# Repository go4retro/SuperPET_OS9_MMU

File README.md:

# SuperPET_OS9_MMU
TPUG OS9 MMU Reproduction

 - [Information and Software](http://mikenaberezny.com/hardware/superpet/super-os9-mmu/)
 - [Purchase a Kit](http://store.go4retro.com/superpet-os-9-mmu/)

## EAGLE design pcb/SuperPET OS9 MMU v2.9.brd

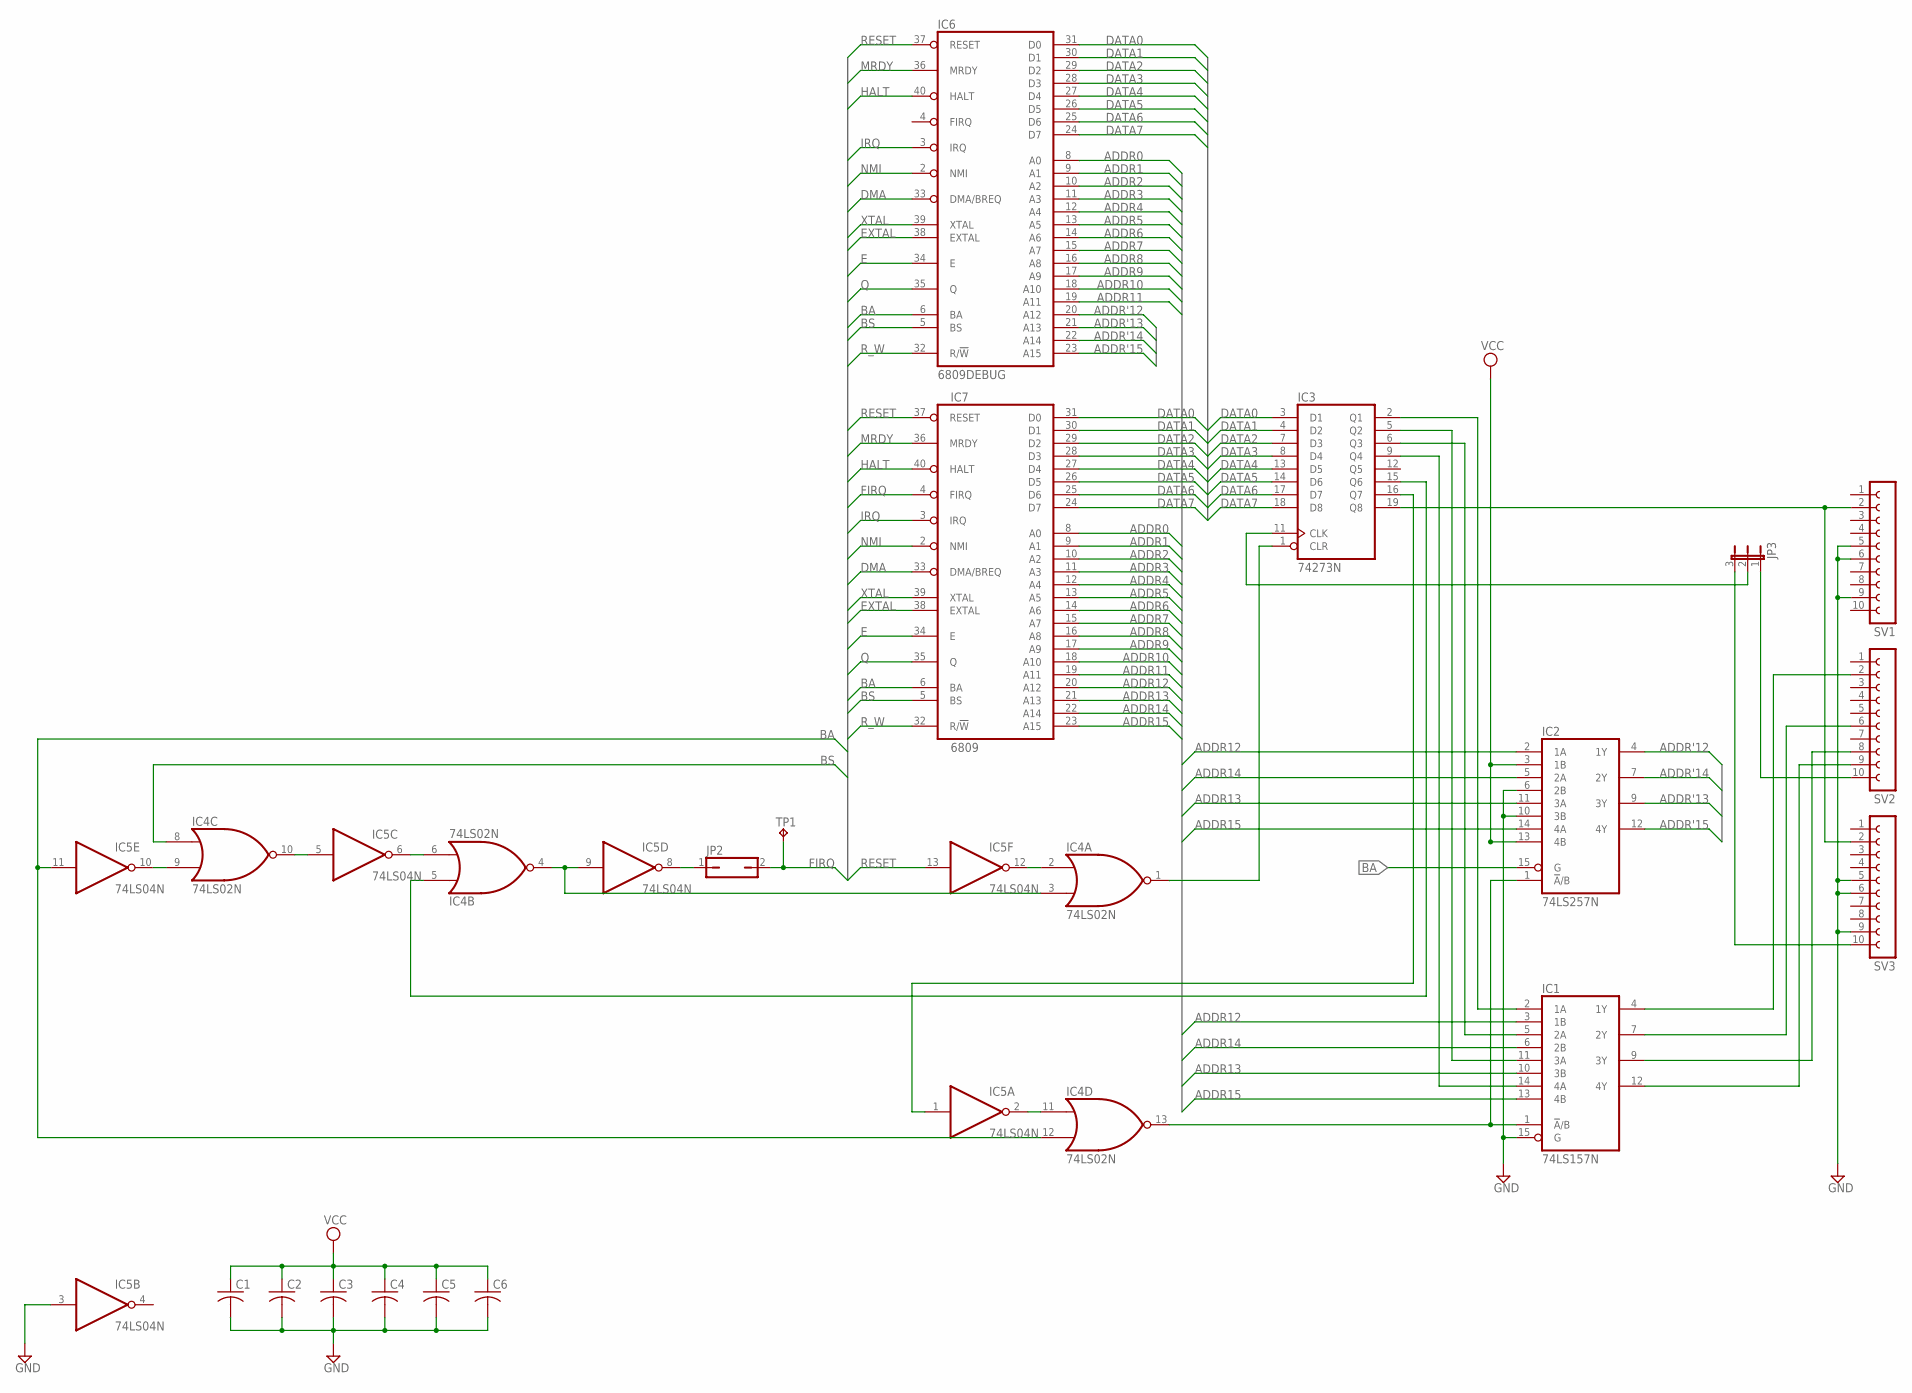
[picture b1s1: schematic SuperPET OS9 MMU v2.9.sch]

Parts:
C1, C2, C3, C4, C5, C6: C-US025-025X050; C025-025X050
IC1: 74LS157N; DIL16
IC2: 74LS257N; DIL16
IC3: 74273N; DIL20
IC4: 74LS02N; DIL14
IC5: 74LS04N; DIL14
IC6: 6809DEBUG; DIL40
IC7: 6809; DIL40
JP2: JP1Q; JP1
JP3: JP2E; JP2
SV1, SV2, SV3: FE10-1; FE10
TP1: TPPAD1-17; P1-17

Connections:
ADDR0: IC6.8 (A0), IC7.8 (A0)
ADDR1: IC6.9 (A1), IC7.9 (A1)
ADDR2: IC6.10 (A2), IC7.10 (A2)
ADDR3: IC6.11 (A3), IC7.11 (A3)
ADDR4: IC6.12 (A4), IC7.12 (A4)
ADDR5: IC6.13 (A5), IC7.13 (A5)
ADDR6: IC6.14 (A6), IC7.14 (A6)
ADDR7: IC6.15 (A7), IC7.15 (A7)
ADDR8: IC6.16 (A8), IC7.16 (A8)
ADDR9: IC6.17 (A9), IC7.17 (A9)
ADDR10: IC6.18 (A10), IC7.18 (A10)
ADDR11: IC6.19 (A11), IC7.19 (A11)
ADDR12: IC1.3 (1B), IC2.2 (1A), IC7.20 (A12)
ADDR13: IC1.10 (3B), IC2.11 (3A), IC7.21 (A13)
ADDR14: IC1.6 (2B), IC2.5 (2A), IC7.22 (A14)
ADDR15: IC1.13 (4B), IC2.14 (4A), IC7.23 (A15)
ADDR'12: IC2.4 (1Y), IC6.20 (A12)
ADDR'13: IC2.9 (3Y), IC6.21 (A13)
ADDR'14: IC2.7 (2Y), IC6.22 (A14)
ADDR'15: IC2.12 (4Y), IC6.23 (A15)
BA: IC2.15 (G), IC4.12 (I1), IC5.11 (I), IC6.6 (BA), IC7.6 (BA)
BS: IC4.8 (I0), IC6.5 (BS), IC7.5 (BS)
DATA0: IC3.3 (D1), IC6.31 (D0), IC7.31 (D0)
DATA1: IC3.4 (D2), IC6.30 (D1), IC7.30 (D1)
DATA2: IC3.7 (D3), IC6.29 (D2), IC7.29 (D2)
DATA3: IC3.8 (D4), IC6.28 (D3), IC7.28 (D3)
DATA4: IC3.13 (D5), IC6.27 (D4), IC7.27 (D4)
DATA5: IC3.14 (D6), IC6.26 (D5), IC7.26 (D5)
DATA6: IC3.17 (D7), IC6.25 (D6), IC7.25 (D6)
DATA7: IC3.18 (D8), IC6.24 (D7), IC7.24 (D7)
DMA: IC6.33 (DMA/BREQ), IC7.33 (DMA/BREQ)
E: IC6.34 (E), IC7.34 (E)
EXTAL: IC6.38 (EXTAL), IC7.38 (EXTAL)
FIRQ: IC7.4 (FIRQ), JP2.2, TP1.1
GND: C1.2, C2.2, C3.2, C4.2, C5.2, C6.2, IC1.8 (GND), IC1.15 (G), IC2.6 (2B), IC2.8 (GND), IC2.10 (3B), IC3.10 (GND), IC4.7 (GND), IC5.3 (I), IC5.7 (GND), IC6.1 (GND), IC7.1 (GND), SV1.5, SV1.6, SV1.9, SV3.5, SV3.6, SV3.9
HALT: IC6.40 (HALT), IC7.40 (HALT)
IRQ: IC6.3 (IRQ), IC7.3 (IRQ)
MRDY: IC6.36 (MRDY), IC7.36 (MRDY)
unnamed: IC1.1 (!A!/B), IC2.1 (!A!/B), IC4.13 (O)
unnamed: IC3.1 (CLR), IC4.1 (O)
unnamed: IC4.2 (I0), IC5.12 (O)
unnamed: IC5.8 (O), JP2.1
unnamed: IC4.3 (I1), IC4.4 (O), IC5.9 (I)
unnamed: IC3.15 (Q6), IC4.5 (I0)
unnamed: IC4.6 (I1), IC5.6 (O)
unnamed: IC4.10 (O), IC5.5 (I)
unnamed: IC4.9 (I1), IC5.10 (O)
unnamed: IC4.11 (I0), IC5.2 (O)
unnamed: IC3.16 (Q7), IC5.1 (I)
unnamed: IC1.2 (1A), IC3.2 (Q1)
unnamed: IC1.14 (4A), IC3.9 (Q4)
unnamed: IC1.11 (3A), IC3.5 (Q2)
unnamed: IC1.7 (2Y), SV2.6
unnamed: IC3.19 (Q8), SV1.2, SV3.2
unnamed: IC1.12 (4Y), SV2.9
unnamed: JP3.1, SV2.10
unnamed: IC3.11 (CLK), JP3.2
unnamed: JP3.3, SV3.10
unnamed: IC1.5 (2A), IC3.6 (Q3)
unnamed: IC1.4 (1Y), SV2.2
unnamed: IC1.9 (3Y), SV2.8
NMI: IC6.2 (NMI), IC7.2 (NMI)
Q: IC6.35 (Q), IC7.35 (Q)
RESET: IC5.13 (I), IC6.37 (RESET), IC7.37 (RESET)
R_W: IC6.32 (R/!W), IC7.32 (R/!W)
VCC: C1.1, C2.1, C3.1, C4.1, C5.1, C6.1, IC1.16 (VCC), IC2.3 (1B), IC2.13 (4B), IC2.16 (VCC), IC3.20 (VCC), IC4.14 (VCC), IC5.14 (VCC), IC6.7 (VCC), IC7.7 (VCC)
XTAL: IC6.39 (XTAL), IC7.39 (XTAL)

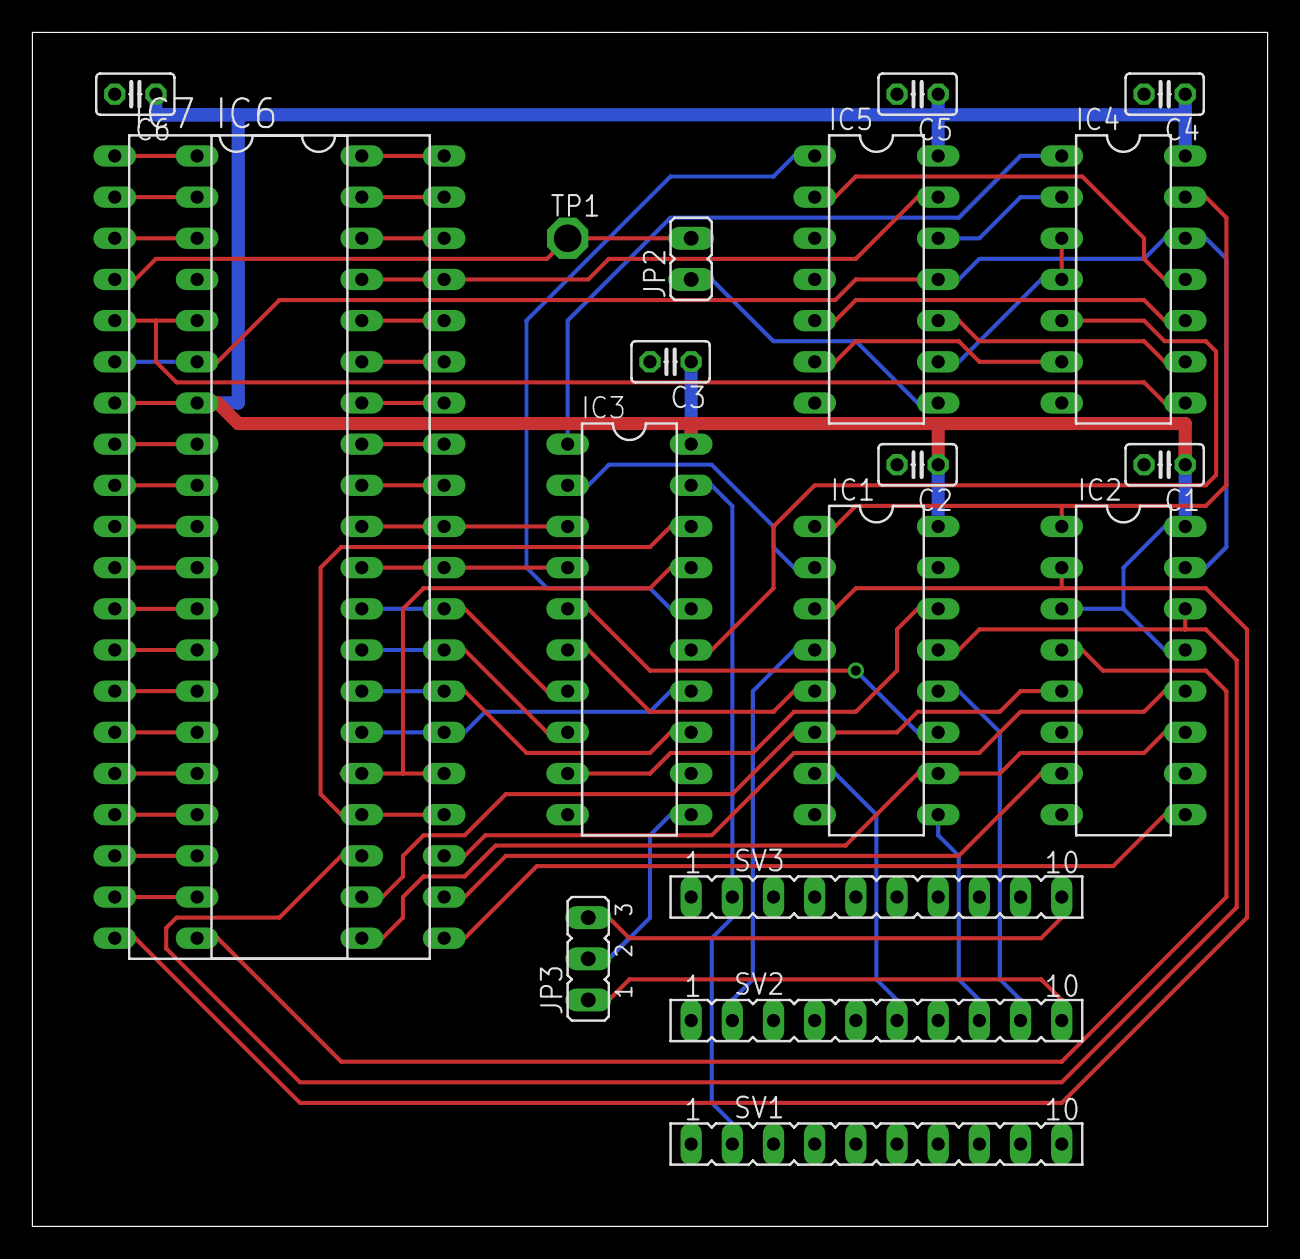
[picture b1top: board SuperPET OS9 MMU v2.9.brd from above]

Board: 2 copper layers, 76.2 x 73.7 mm, 19 parts (0 on the bottom side), 67 nets.

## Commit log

2018-03-10 Add links to info and kit
2018-05-06 Added .gitignore
